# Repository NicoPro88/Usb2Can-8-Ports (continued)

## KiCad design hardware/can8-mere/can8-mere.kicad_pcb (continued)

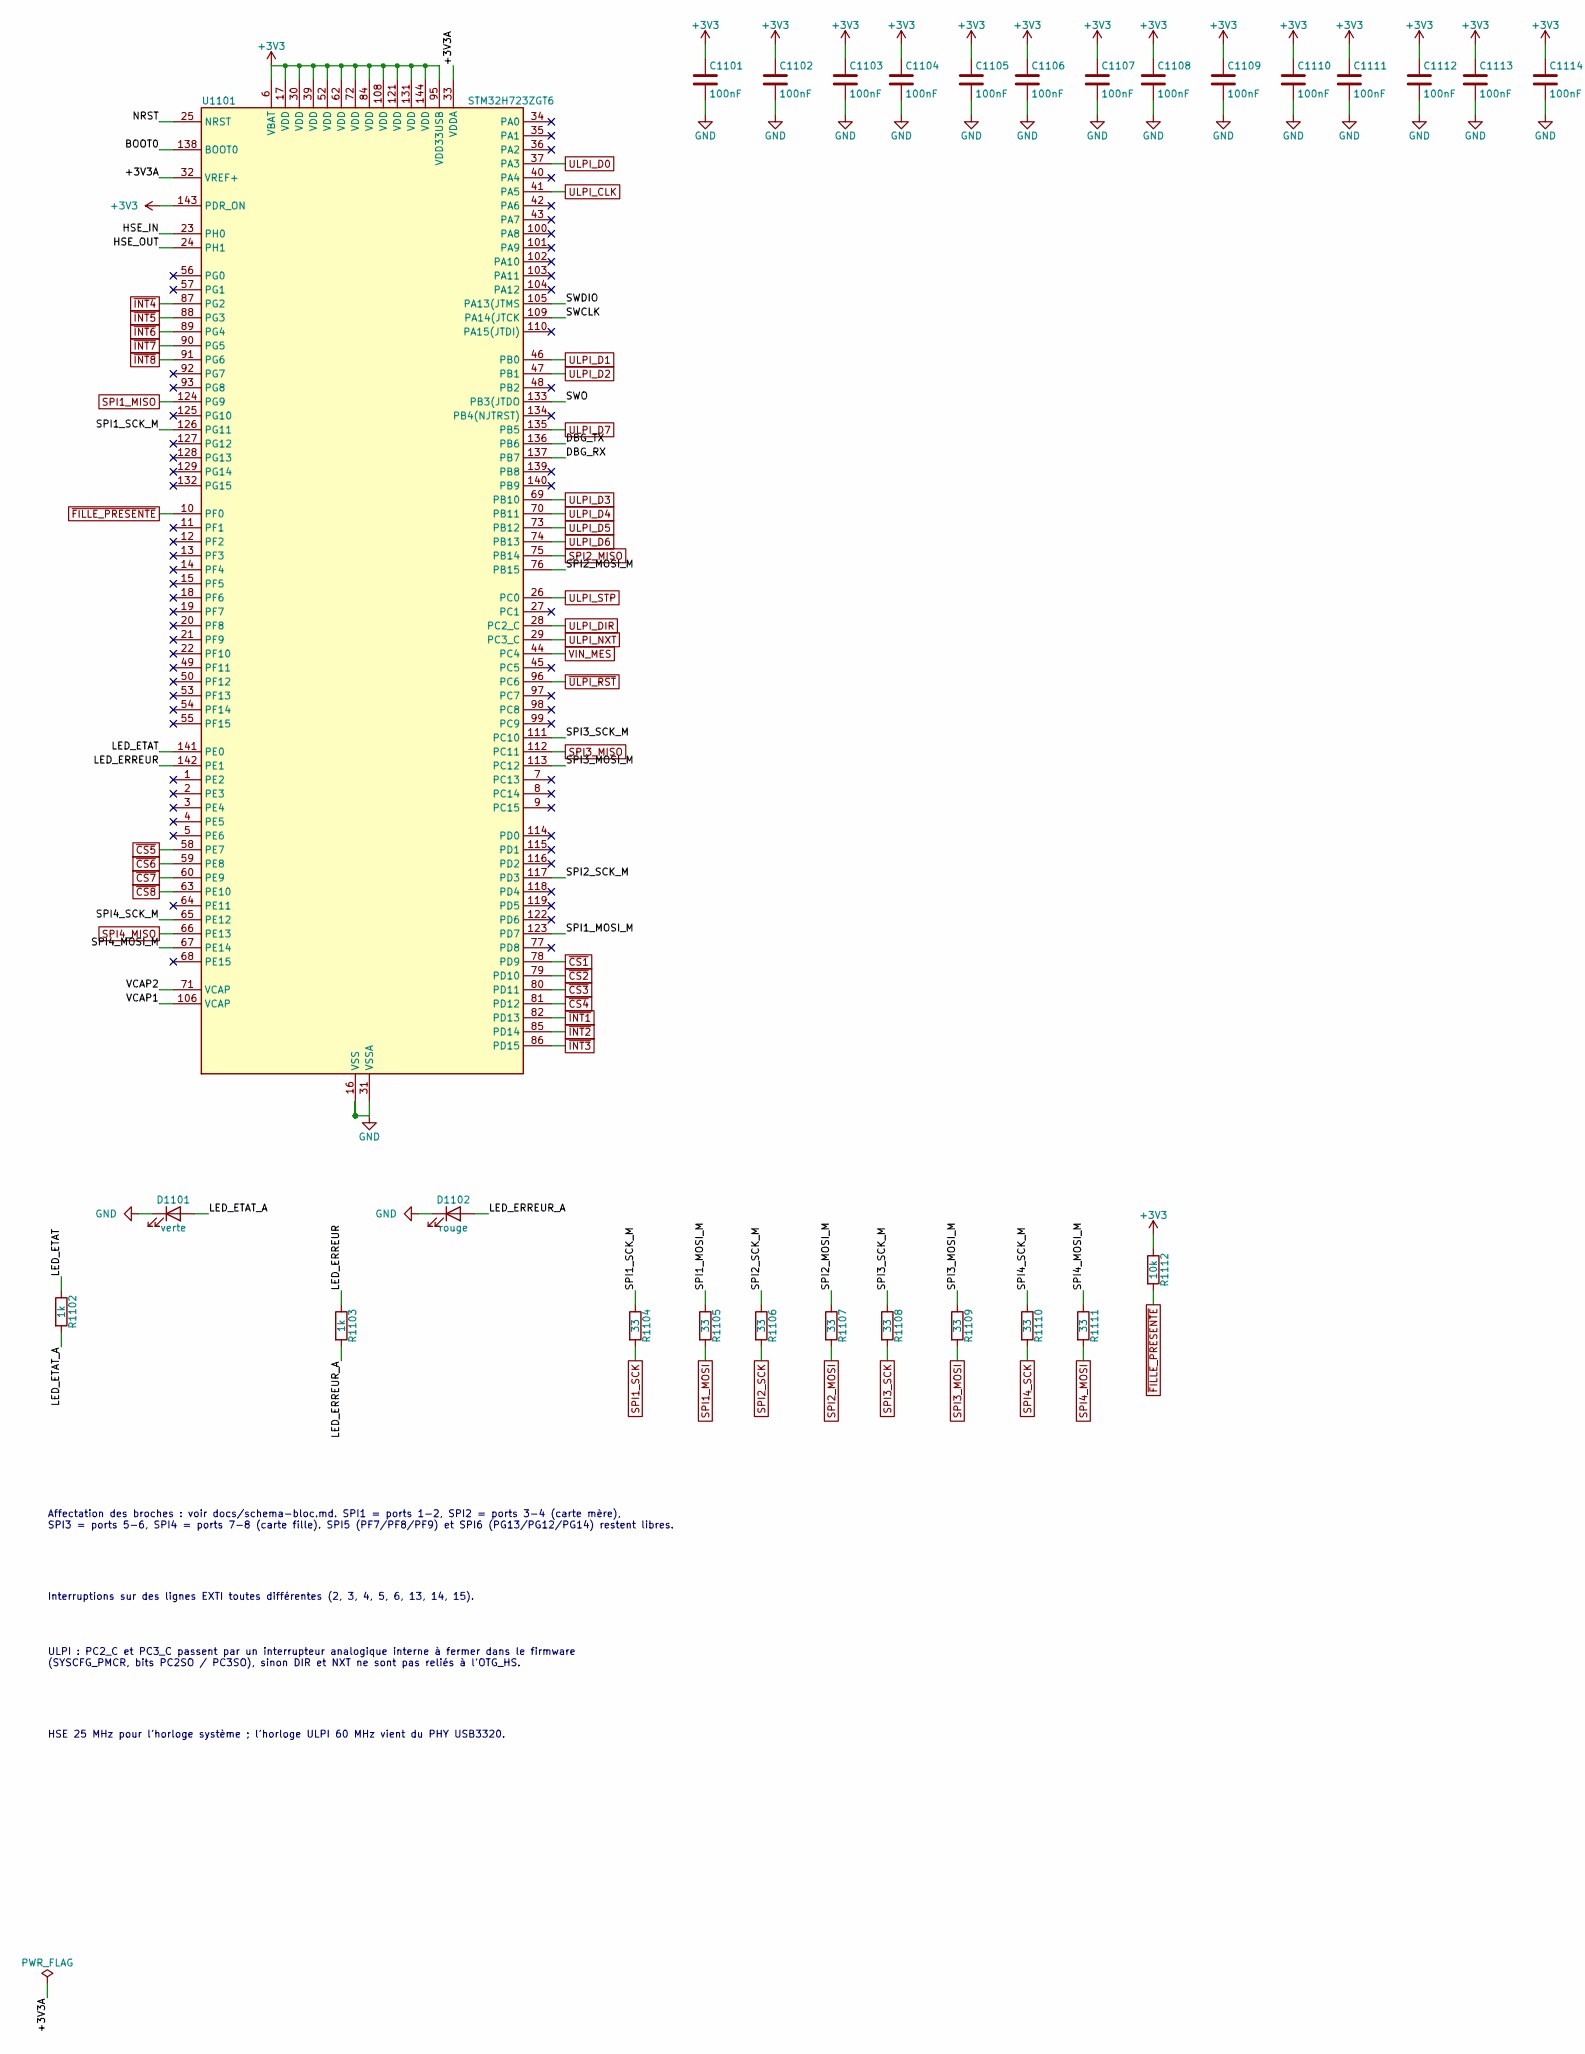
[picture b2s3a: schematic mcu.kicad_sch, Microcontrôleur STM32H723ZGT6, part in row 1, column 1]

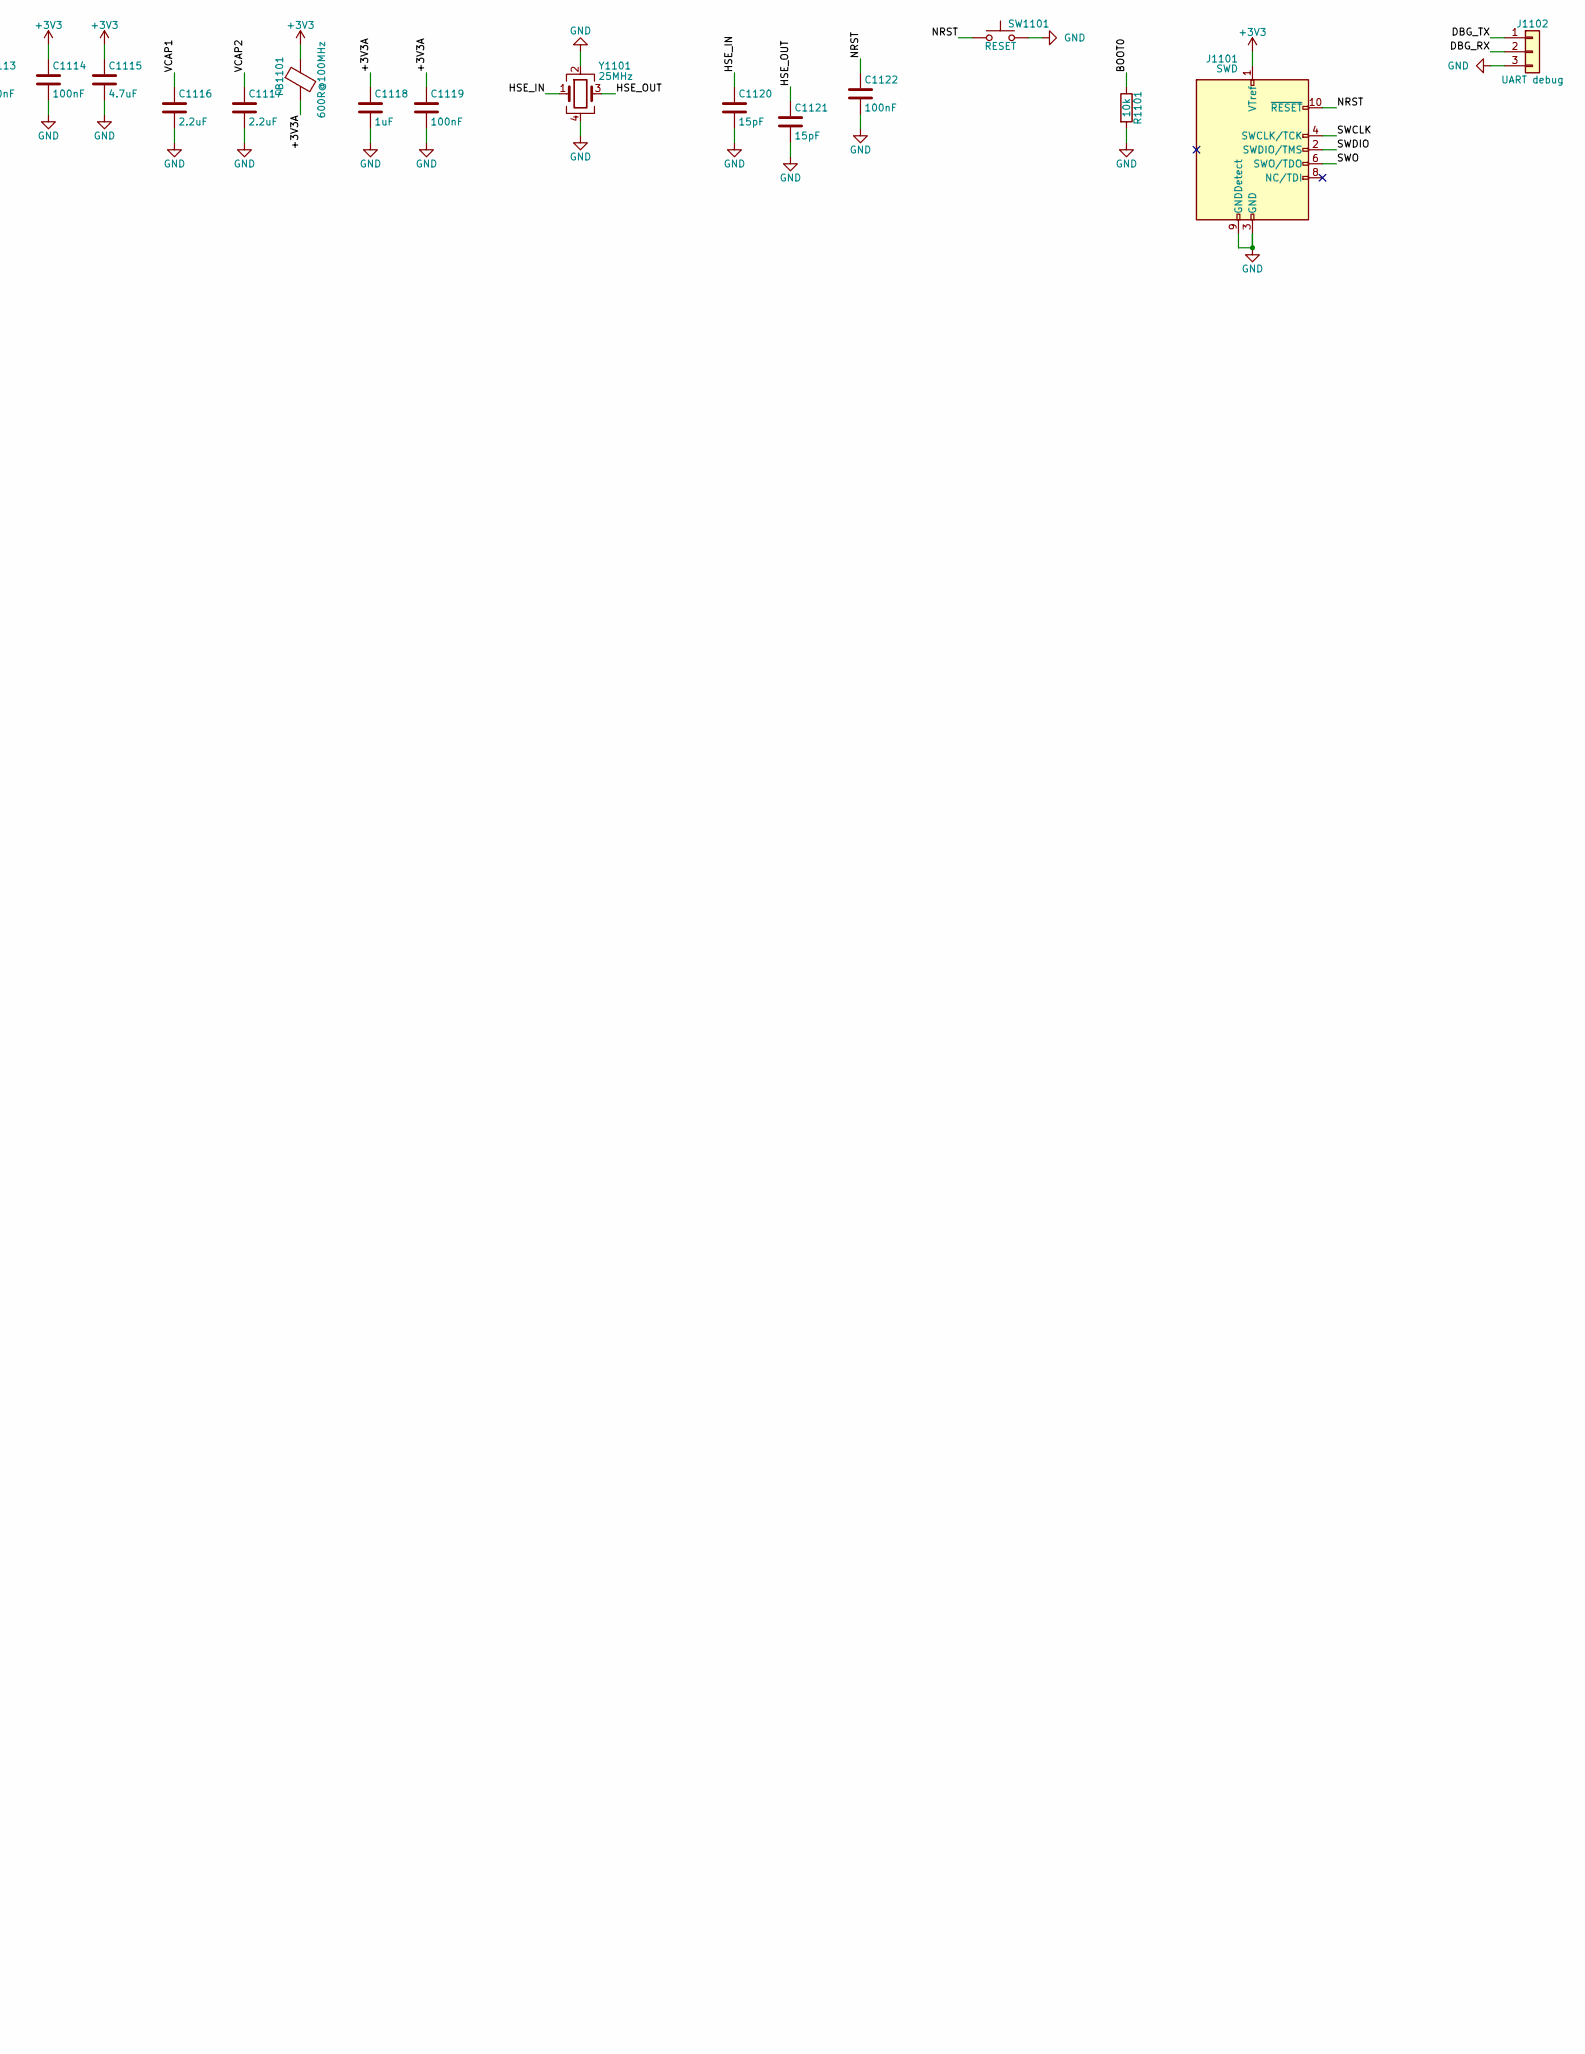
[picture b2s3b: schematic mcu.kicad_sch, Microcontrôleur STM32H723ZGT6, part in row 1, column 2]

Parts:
C1101, C1102, C1103, C1104, C1105, C1106, C1107, C1108, C1109, C1110, C1111, C1112, C1113, C1114, C1119, C1122: 100nF; C_0603_1608Metric
C1115: 4.7uF; C_0805_2012Metric
C1116, C1117: 2.2uF; C_0805_2012Metric
C1118: 1uF; C_0805_2012Metric
C1120, C1121: 15pF; C_0603_1608Metric
D1101: verte; LED_0603_1608Metric
D1102: rouge; LED_0603_1608Metric
FB1101: 600R@100MHz; L_0603_1608Metric
J1101: SWD; PinHeader_2x05_P1.27mm_Vertical
J1102: UART debug; PinHeader_1x03_P2.54mm_Vertical
R1101, R1112: 10k; R_0603_1608Metric
R1102, R1103: 1k; R_0603_1608Metric
R1104, R1105, R1106, R1107, R1108, R1109, R1110, R1111: 33; R_0603_1608Metric
SW1101: RESET; SW_SPST_B3U-1000P
U1101: STM32H723ZGT6; LQFP-144_20x20mm_P0.5mm
Y1101: 25MHz; Crystal_SMD_3225-4Pin_3.2x2.5mm

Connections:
+3V3: C1101.1, C1102.1, C1103.1, C1104.1, C1105.1, C1106.1, C1107.1, C1108.1, C1109.1, C1110.1, C1111.1, C1112.1, C1113.1, C1114.1, C1115.1, FB1101.1, J1101.1 (VTref), R1112.1, U1101.6 (VBAT), U1101.17 (VDD), U1101.30 (VDD), U1101.39 (VDD), U1101.52 (VDD), U1101.62 (VDD), U1101.72 (VDD), U1101.84 (VDD), U1101.95 (VDD33USB), U1101.108 (VDD), U1101.121 (VDD), U1101.131 (VDD), U1101.143 (PDR_ON), U1101.144 (VDD); also elsewhere on the board
/Microcontrôleur STM32H723ZGT6/+3V3A: C1118.1, C1119.1, FB1101.2, U1101.32 (VREF+), U1101.33 (VDDA)
/Microcontrôleur STM32H723ZGT6/BOOT0: R1101.1, U1101.138 (BOOT0)
/Microcontrôleur STM32H723ZGT6/DBG_RX: J1102.2, U1101.137 (PB7)
/Microcontrôleur STM32H723ZGT6/DBG_TX: J1102.1, U1101.136 (PB6)
/Microcontrôleur STM32H723ZGT6/HSE_IN: C1120.1, U1101.23 (PH0), Y1101.1
/Microcontrôleur STM32H723ZGT6/HSE_OUT: C1121.1, U1101.24 (PH1), Y1101.3
/Microcontrôleur STM32H723ZGT6/LED_ERREUR: R1103.1, U1101.142 (PE1)
/Microcontrôleur STM32H723ZGT6/LED_ERREUR_A: D1102.2 (A), R1103.2
/Microcontrôleur STM32H723ZGT6/LED_ETAT: R1102.1, U1101.141 (PE0)
/Microcontrôleur STM32H723ZGT6/LED_ETAT_A: D1101.2 (A), R1102.2
/Microcontrôleur STM32H723ZGT6/NRST: C1122.1, J1101.10 (~RESET), SW1101.1, U1101.25 (NRST)
/Microcontrôleur STM32H723ZGT6/SPI1_MOSI_M: R1105.1, U1101.123 (PD7)
/Microcontrôleur STM32H723ZGT6/SPI1_SCK_M: R1104.1, U1101.126 (PG11)
/Microcontrôleur STM32H723ZGT6/SPI2_MOSI_M: R1107.1, U1101.76 (PB15)
/Microcontrôleur STM32H723ZGT6/SPI2_SCK_M: R1106.1, U1101.117 (PD3)
/Microcontrôleur STM32H723ZGT6/SPI3_MOSI_M: R1109.1, U1101.113 (PC12)
/Microcontrôleur STM32H723ZGT6/SPI3_SCK_M: R1108.1, U1101.111 (PC10)
/Microcontrôleur STM32H723ZGT6/SPI4_MOSI_M: R1111.1, U1101.67 (PE14)
/Microcontrôleur STM32H723ZGT6/SPI4_SCK_M: R1110.1, U1101.65 (PE12)
/Microcontrôleur STM32H723ZGT6/SWCLK: J1101.4 (SWCLK/TCK), U1101.109 (PA14(JTCK)
/Microcontrôleur STM32H723ZGT6/SWDIO: J1101.2 (SWDIO/TMS), U1101.105 (PA13(JTMS)
/Microcontrôleur STM32H723ZGT6/SWO: J1101.6 (SWO/TDO), U1101.133 (PB3(JTDO)
/Microcontrôleur STM32H723ZGT6/VCAP1: C1116.1, U1101.106 (VCAP)
/Microcontrôleur STM32H723ZGT6/VCAP2: C1117.1, U1101.71 (VCAP)
GND: C1101.2, C1102.2, C1103.2, C1104.2, C1105.2, C1106.2, C1107.2, C1108.2, C1109.2, C1110.2, C1111.2, C1112.2, C1113.2, C1114.2, C1115.2, C1116.2, C1117.2, C1118.2, C1119.2, C1120.2, C1121.2, C1122.2, D1101.1 (K), D1102.1 (K), J1101.3 (GND), J1101.5 (GND), J1101.9 (GNDDetect), J1102.3, R1101.2, SW1101.2, U1101.16 (VSS), U1101.31 (VSSA), U1101.38 (VSS), U1101.51 (VSS), U1101.61 (VSS), U1101.83 (VSS), U1101.94 (VSS), U1101.107 (VSS), U1101.120 (VSS), U1101.130 (VSS), Y1101.2, Y1101.4; also elsewhere on the board
SPI1_MISO: U1101.124 (PG9); also elsewhere on the board
SPI1_MOSI: R1105.2; also elsewhere on the board
SPI1_SCK: R1104.2; also elsewhere on the board
SPI2_MISO: U1101.75 (PB14); also elsewhere on the board
SPI2_MOSI: R1107.2; also elsewhere on the board
SPI2_SCK: R1106.2; also elsewhere on the board
SPI3_MISO: U1101.112 (PC11); also elsewhere on the board
SPI3_MOSI: R1109.2; also elsewhere on the board
SPI3_SCK: R1108.2; also elsewhere on the board
SPI4_MISO: U1101.66 (PE13); also elsewhere on the board
SPI4_MOSI: R1111.2; also elsewhere on the board
SPI4_SCK: R1110.2; also elsewhere on the board
ULPI_CLK: U1101.41 (PA5); also elsewhere on the board
ULPI_D0: U1101.37 (PA3); also elsewhere on the board
ULPI_D1: U1101.46 (PB0); also elsewhere on the board
ULPI_D2: U1101.47 (PB1); also elsewhere on the board
ULPI_D3: U1101.69 (PB10); also elsewhere on the board
ULPI_D4: U1101.70 (PB11); also elsewhere on the board
ULPI_D5: U1101.73 (PB12); also elsewhere on the board
ULPI_D6: U1101.74 (PB13); also elsewhere on the board
ULPI_D7: U1101.135 (PB5); also elsewhere on the board
ULPI_DIR: U1101.28 (PC2_C); also elsewhere on the board
ULPI_NXT: U1101.29 (PC3_C); also elsewhere on the board
ULPI_STP: U1101.26 (PC0); also elsewhere on the board
VIN_MES: U1101.44 (PC4); also elsewhere on the board
~CS1: U1101.78 (PD9); also elsewhere on the board
~CS2: U1101.79 (PD10); also elsewhere on the board
~CS3: U1101.80 (PD11); also elsewhere on the board
~CS4: U1101.81 (PD12); also elsewhere on the board
~CS5: U1101.58 (PE7); also elsewhere on the board
~CS6: U1101.59 (PE8); also elsewhere on the board
~CS7: U1101.60 (PE9); also elsewhere on the board
~CS8: U1101.63 (PE10); also elsewhere on the board
~FILLE_PRESENTE: R1112.2, U1101.10 (PF0); also elsewhere on the board
~INT1: U1101.56 (PG0); also elsewhere on the board
~INT2: U1101.57 (PG1); also elsewhere on the board
~INT3: U1101.103 (PA11); also elsewhere on the board
~INT4: U1101.87 (PG2); also elsewhere on the board
~INT5: U1101.88 (PG3); also elsewhere on the board
~INT6: U1101.89 (PG4); also elsewhere on the board
~INT7: U1101.90 (PG5); also elsewhere on the board
~INT8: U1101.91 (PG6); also elsewhere on the board
~ULPI_RST: U1101.96 (PC6); also elsewhere on the board

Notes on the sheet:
Affectation des broches : voir docs/schema-bloc.md. SPI1 = ports 1-2, SPI2 = ports 3-4 (carte mère), SPI3 = ports 5-6, SPI4 = ports 7-8 (carte fille). SPI5 (PF7/PF8/PF9) et SPI6 (PG13/PG12/PG14) restent libres.
Interruptions sur des lignes EXTI toutes différentes (2, 3, 4, 5, 6, 13, 14, 15).
ULPI : PC2_C et PC3_C passent par un interrupteur analogique interne à fermer dans le firmware (SYSCFG_PMCR, bits PC2SO / PC3SO), sinon DIR et NXT ne sont pas reliés à l'OTG_HS.
HSE 25 MHz pour l'horloge système ; l'horloge ULPI 60 MHz vient du PHY USB3320.

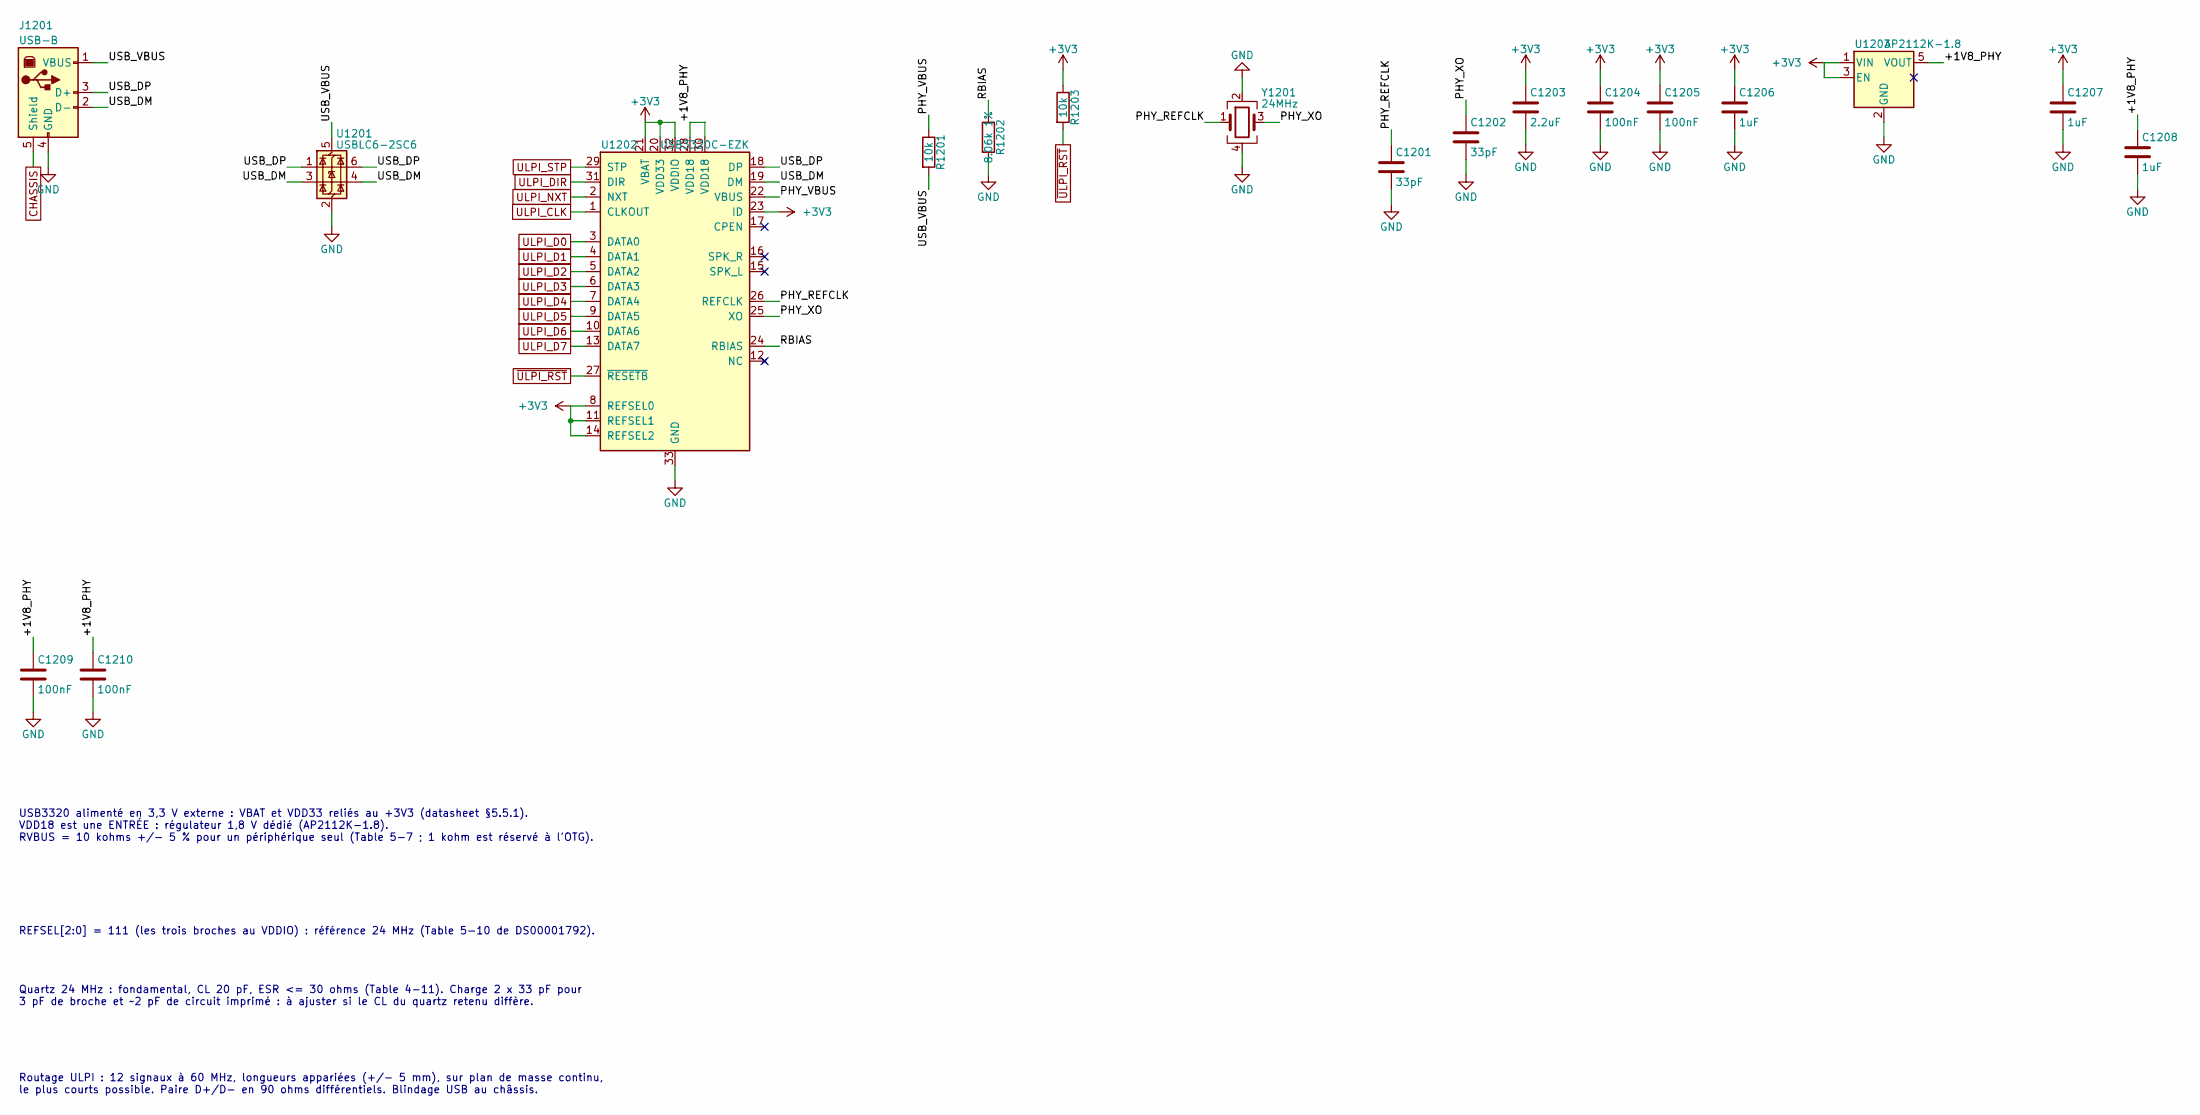
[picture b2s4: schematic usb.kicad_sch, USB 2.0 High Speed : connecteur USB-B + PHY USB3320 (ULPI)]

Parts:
C1201, C1202: 33pF; C_0603_1608Metric
C1203: 2.2uF; C_0805_2012Metric
C1204, C1205, C1209, C1210: 100nF; C_0603_1608Metric
C1206, C1207, C1208: 1uF; C_0805_2012Metric
J1201: USB-B; USB_B_OST_USB-B1HSxx_Horizontal
R1201, R1203: 10k; R_0603_1608Metric
R1202: 8.06k 1%; R_0603_1608Metric
U1201: USBLC6-2SC6; SOT-23-6
U1202: USB3320C-EZK; QFN-32-1EP_5x5mm_P0.5mm_EP3.3x3.3mm
U1203: AP2112K-1.8; SOT-23-5
Y1201: 24MHz; Crystal_SMD_3225-4Pin_3.2x2.5mm

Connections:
+3V3: C1203.1, C1204.1, C1205.1, C1206.1, C1207.1, R1203.1, U1202.8 (REFSEL0), U1202.11 (REFSEL1), U1202.14 (REFSEL2), U1202.20 (VDD33), U1202.21 (VBAT), U1202.23 (ID), U1202.32 (VDDIO), U1203.1 (VIN), U1203.3 (EN); also elsewhere on the board
/USB 2.0 High Speed /+1V8_PHY: C1208.1, C1209.1, C1210.1, U1202.28 (VDD18), U1202.30 (VDD18), U1203.5 (VOUT)
/USB 2.0 High Speed /PHY_REFCLK: C1201.1, U1202.26 (REFCLK), Y1201.1
/USB 2.0 High Speed /PHY_VBUS: R1201.1, U1202.22 (VBUS)
/USB 2.0 High Speed /PHY_XO: C1202.1, U1202.25 (XO), Y1201.3
/USB 2.0 High Speed /RBIAS: R1202.1, U1202.24 (RBIAS)
/USB 2.0 High Speed /USB_DM: J1201.2 (D-), U1201.3 (I/O2), U1201.4 (I/O2), U1202.19 (DM)
/USB 2.0 High Speed /USB_DP: J1201.3 (D+), U1201.1 (I/O1), U1201.6 (I/O1), U1202.18 (DP)
/USB 2.0 High Speed /USB_VBUS: J1201.1 (VBUS), R1201.2, U1201.5 (VBUS)
CHASSIS: J1201.5 (Shield); also elsewhere on the board
GND: C1201.2, C1202.2, C1203.2, C1204.2, C1205.2, C1206.2, C1207.2, C1208.2, C1209.2, C1210.2, J1201.4 (GND), R1202.2, U1201.2 (GND), U1202.33 (GND), U1203.2 (GND), Y1201.2, Y1201.4; also elsewhere on the board
ULPI_CLK: U1202.1 (CLKOUT); also elsewhere on the board
ULPI_D0: U1202.3 (DATA0); also elsewhere on the board
ULPI_D1: U1202.4 (DATA1); also elsewhere on the board
ULPI_D2: U1202.5 (DATA2); also elsewhere on the board
ULPI_D3: U1202.6 (DATA3); also elsewhere on the board
ULPI_D4: U1202.7 (DATA4); also elsewhere on the board
ULPI_D5: U1202.9 (DATA5); also elsewhere on the board
ULPI_D6: U1202.10 (DATA6); also elsewhere on the board
ULPI_D7: U1202.13 (DATA7); also elsewhere on the board
ULPI_DIR: U1202.31 (DIR); also elsewhere on the board
ULPI_NXT: U1202.2 (NXT); also elsewhere on the board
ULPI_STP: U1202.29 (STP); also elsewhere on the board
~ULPI_RST: R1203.2, U1202.27 (~RESETB); also elsewhere on the board

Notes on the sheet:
USB3320 alimenté en 3,3 V externe : VBAT et VDD33 reliés au +3V3 (datasheet §5.5.1). VDD18 est une ENTRÉE : régulateur 1,8 V dédié (AP2112K-1.8). RVBUS = 10 kohms +/- 5 % pour un périphérique seul (Table 5-7 ; 1 kohm est réservé à l'OTG).
REFSEL[2:0] = 111 (les trois broches au VDDIO) : référence 24 MHz (Table 5-10 de DS00001792).
Quartz 24 MHz : fondamental, CL 20 pF, ESR <= 30 ohms (Table 4-11). Charge 2 x 33 pF pour 3 pF de broche et ~2 pF de circuit imprimé : à ajuster si le CL du quartz retenu diffère.
Routage ULPI : 12 signaux à 60 MHz, longueurs appariées (+/- 5 mm), sur plan de masse continu, le plus courts possible. Paire D+/D- en 90 ohms différentiels. Blindage USB au châssis.

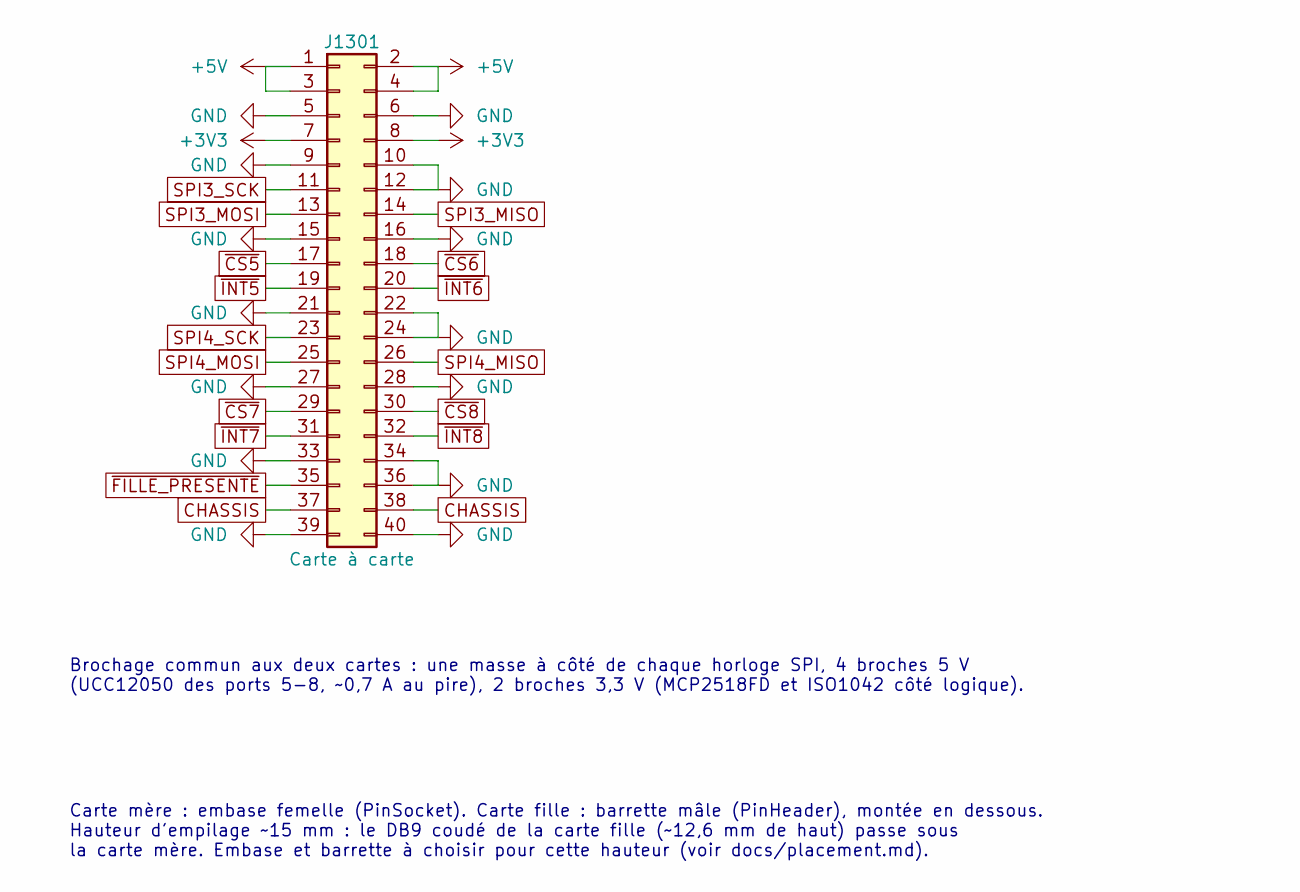
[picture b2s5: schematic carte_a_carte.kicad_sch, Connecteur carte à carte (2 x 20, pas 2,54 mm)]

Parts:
J1301: Carte à carte; PinSocket_2x20_P2.54mm_Vertical

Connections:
+3V3: J1301.7, J1301.8; also elsewhere on the board
+5V: J1301.1, J1301.2, J1301.3, J1301.4; also elsewhere on the board
CHASSIS: J1301.37, J1301.38; also elsewhere on the board
GND: J1301.5, J1301.6, J1301.9, J1301.10, J1301.12, J1301.15, J1301.16, J1301.21, J1301.22, J1301.24, J1301.27, J1301.28, J1301.33, J1301.34, J1301.36, J1301.39, J1301.40; also elsewhere on the board
SPI3_MISO: J1301.14; also elsewhere on the board
SPI3_MOSI: J1301.13; also elsewhere on the board
SPI3_SCK: J1301.11; also elsewhere on the board
SPI4_MISO: J1301.26; also elsewhere on the board
SPI4_MOSI: J1301.25; also elsewhere on the board
SPI4_SCK: J1301.23; also elsewhere on the board
~CS5: J1301.17; also elsewhere on the board
~CS6: J1301.18; also elsewhere on the board
~CS7: J1301.29; also elsewhere on the board
~CS8: J1301.30; also elsewhere on the board
~FILLE_PRESENTE: J1301.35; also elsewhere on the board
~INT5: J1301.19; also elsewhere on the board
~INT6: J1301.20; also elsewhere on the board
~INT7: J1301.31; also elsewhere on the board
~INT8: J1301.32; also elsewhere on the board

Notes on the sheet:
Brochage commun aux deux cartes : une masse à côté de chaque horloge SPI, 4 broches 5 V (UCC12050 des ports 5-8, ~0,7 A au pire), 2 broches 3,3 V (MCP2518FD et ISO1042 côté logique).
Carte mère : embase femelle (PinSocket). Carte fille : barrette mâle (PinHeader), montée en dessous. Hauteur d'empilage ~15 mm : le DB9 coudé de la carte fille (~12,6 mm de haut) passe sous la carte mère. Embase et barrette à choisir pour cette hauteur (voir docs/placement.md).
